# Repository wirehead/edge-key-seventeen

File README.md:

# edge-key-seventeen: A 17 key standard-layout numeric keypad plus encoders

I like numeric keypads.  They come in handy when I am working with CAD packages and stuff.  So you can see this as a piece of quiet rebellion against the world of hipster 40% or 60% fancy keyboards but one that still gives you a durable, fancy, interesting, artisanal, hand-crafted, mechanically-keyed product at the end of it.

## Prior art

This is partially developed using [Ruiqi Mao's Keyboard PCB guide](https://github.com/ruiqimao/keyboard-pcb-guide) as a reference... except that I'd suggest you don't actually use that guide as a reference because it's got some inaccuracies and at this point is old and unmaintained.  It turns out that, because I was designing it around parts that I already was comfortable with using and based it off of prior designs, I'd managed to sidestep all of the problems.  The current hotness is arguably the [ai03 Keyboard PCB](https://wiki.ai03.com/books/pcb-design) guide which seems to be newer and more accurate.

Otherwise, this has design lineage through a few earlier designs I cooked up but won't bother posting because they were mostly design experiments and aren't really useful for anyone.

## The design

### Design goals

* Be mostly standard in being designed for the QMK firmware, use Cherry MX keyswitches and standard-sized keycaps, etc.
* Contain the 17 keys of a numeric keypad, plus maybe some encoders for the funs.
* Look vaguely interesting as just a PCB.
* Use parts I already had in my parts bin for other projects.

### Concrete technical spec

* 17 keys in the standard layout so you can use pretty much any standard-layout numeric keypad caps.
* 2 rotary encoders with push-buttons.
* ATMega32u4 processor
* USB-C port
* Extra ESD protection diodes and a polyfuse for durability
* Programming port that you shouldn't actually need to ever use.
* 9 4-pin SK6812 "NeoPixel" RGB LEDs pointed downward for underglow
* 6 M2.5 mounting holes
* Not quite able to fit in the 10cm x 10cm box because of the size of the keys.
* Puns on the silkscreen

### USB protection

I did a bunch of digging and datasheet reading.

Given that I'm plugging this into the USB port on my computer, I tend to go for safety.  Thus, there's a ESD diode to protect the USB lines from spikes, there's a polyfuse on the power line so it won't use too much power, there's the required capacitors, and there's a decoupling network to keep the EMI from the cable sheath from crossing over to the ground plane.  This is more than most of the development boards.

I also added a polyfuse in case you short power to ground so it will reduce the chances that things go really bad.

### Routing scheme

Col: PF0, PD4, PD5, PD3, PD2
Row: PB6, PC7, PC6. PB5, PB4
Encoders: PF5/PF6, PF1/PF4
Col -> Row

Neopixel: PB7

Numlock LED: PF7

## BOM

|Reference	 |Quantity	 |Value	 |Footprint|
|------------|-----------|-------|---------|
|C10 	| 1	| 4.7 nF	| 0805 |
|C1,C2 	| 2	| 22 pF	| 0805 |
|C3 	| 1	| 10 uF	| 0805 |
|C4 	| 1	| 1 uF	| 0805 |
|C5,C6,C7,C8 	| 4	| 0.1 uF	| 0805 | 
|D1,D2,D3,D4,D5,D6,D7,D9,D10,D11,D12,D13,D14,D15,D16,D17,D18,D27,D28 | 19	1N4148	| SOD123 / Axial |
|D19,D20,D21,D22,D23,D24,D25,D26,D29 	| 9	| SK6812	| 5050 PLCC4 |
|D30    | 1 | 5mm LED | |
|D8 	| 1	| PRTR5V0U2X_215	| TO-253-4 |
|F1 	| 1	| 500 mA Polyfuse	| 1206 |
|H1-H6 	| 6	| Mounting Hole	| M2.5 |
|J1 	| 1	| MicroUSB	| GCT USB4085-GF-A |
|J2 	| 1	| AVR-ISP-6	| 2x03 2.54mm pitch vertical SMD |
|MX1,MX2,MX3,MX4,MX5,MX6,MX7,MX9,MX10,MX11,MX12,MX13,MX14,MX17 | 14	| Cherry MX	|1U |
|MX8 MX15 	| 2	| Cherry MX	| 2U Vertical |
|MX16 	| 1	| Cherry MX	| 2U Horizontal |
|R1 	| 1	| 1M | 0603 |
|R2,R3 	| 2	| 22 | 0603 |
|R4,R5	| 2	| 10k | 0805 |
|R6,R8  | 2 | 5.1k | 0603 | 
|R7 | 1	| 1 M | 0603 |
|R9,R10 | 1	| 330 | 0805 |
|S1 | 1	| Toggle switch	| C&K KSR223GLFG | 
|SW1,SW2 | 2	| Rotary_Encoder_Switch	| PEC11R-4215F-S0024-0-0-0 |
|U1 | 1	| ATMEGA32U4 | TQFP-44 |
|Y1 | 1	| 16 MHz | HC49-U |

## Construction

The gerber files are as I upload to JLCPCB to be fabbed.

If other people start wanting to try and fab this board, I'll write an actual proper assembly guide. :)

Either way, the important points to consider are:

* Everything should be solderable with a regular old temperature-controlled ESD-protected soldering iron.
* You don't need to populate J2 unless you get yourself in deep trouble.
* The keyboard diodes are hybrid footprints that can use either a SOD-123 surface mount diode or an axial one.  I actually find SOD-123's easier to solder all told but I'm probably at least a bit odd.
* You can use either PCB-mount or plate-mount keyswitches and there are holes for PCB-mounted stabilizers.
* You can use a set of Mill-Max 7305-0-15-15-47-27-10-0 maybe the new 3305-1-15-15-47-27-10-0 receptacle connectors so that the keyswitches can be hot-swapped -- The 3305-X series is a new part specifically designed for keyswitches.

### Initial bootstrapping

You should just be able to program a freshly constructed board to the USB port and use the QMK programming tool to put an appropriate firmware on the board with the default bootloader.

I need to actually submit the upstream patches for QMK.

### Mounting holes

There are 6 M2.5 sized mounting holes in semi-convenient locations.

### Chassis design

This will appear later, still working on it!

## Changelog

### v1.0 rev 1

### v1.0 rev 2

* MicroUSB replaced with USB-C
* RS-187R05A2-DS button replaced with KSR223G LFG
* RG-49 Crystal a 3.2x2.5mm SMT 
* KiCAD 6.x instead of KiCAD 5.x

### Things I would change next time

* I might try to trim a few mm off of each of the edges.
* I might remove the hybrid SOD123/Axial feature because I actually solder SOD123's faster than I solder axial parts these days.
* The programming port is kinda annoying in the layout and I guess I need to look at more alternatives in the rare case you need to bootloader it.

## License

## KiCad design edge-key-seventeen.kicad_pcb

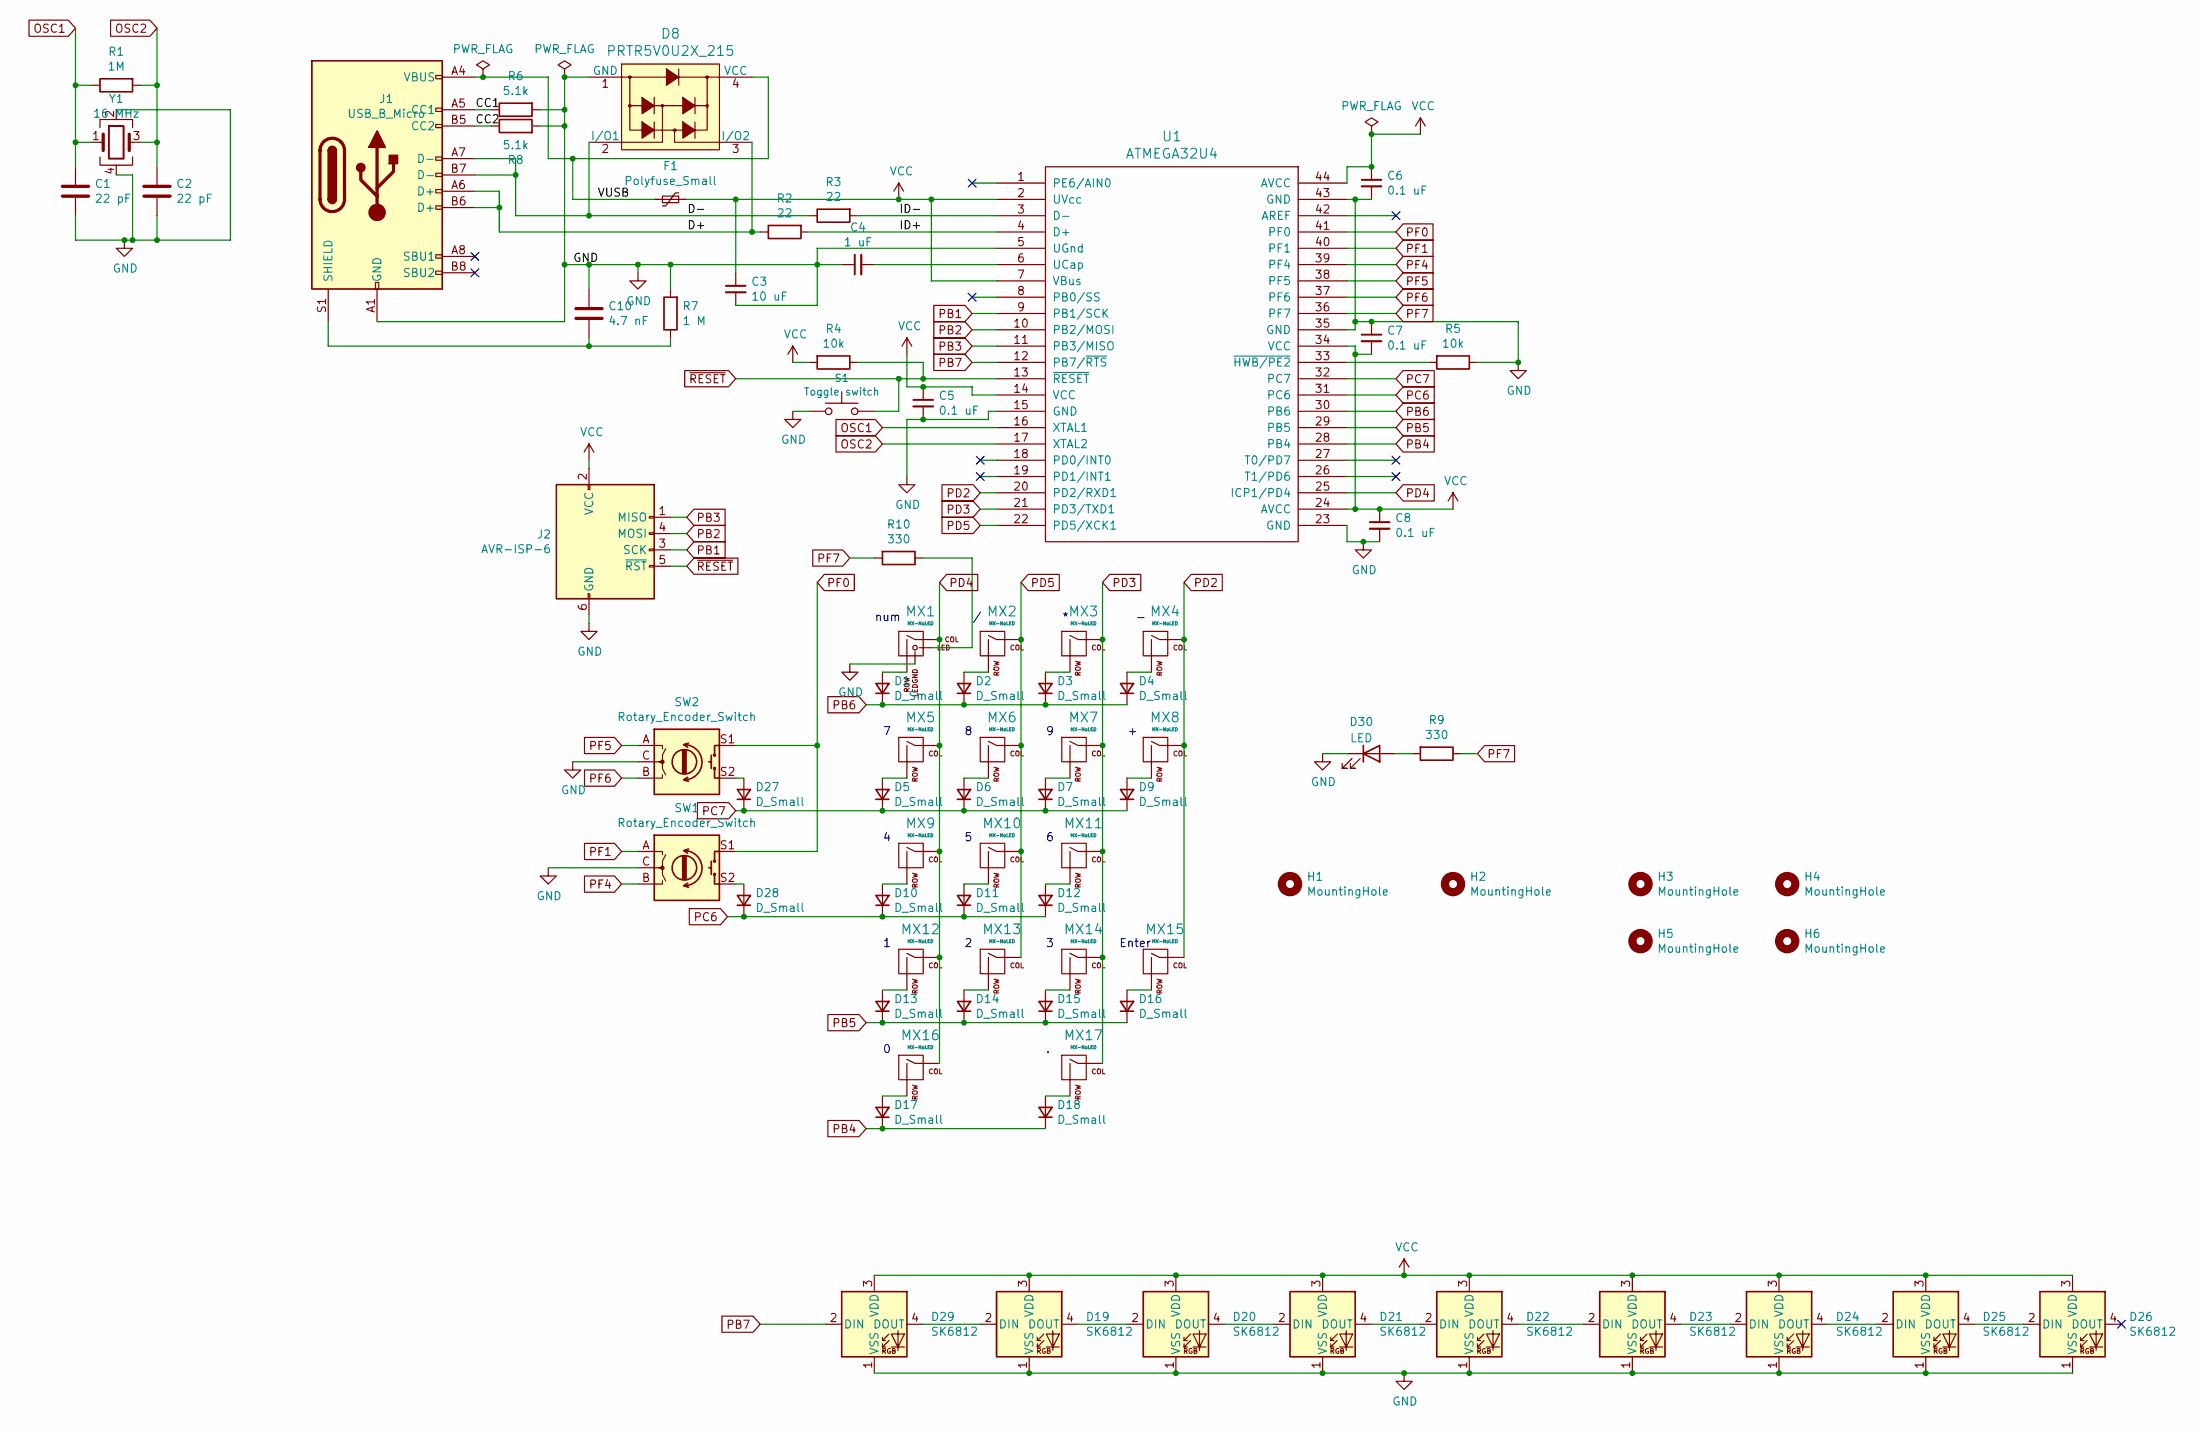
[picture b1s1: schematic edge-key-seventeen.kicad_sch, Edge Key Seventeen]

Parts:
C1, C2: 22 pF; C_0805_2012Metric_Pad1.15x1.40mm_HandSolder
C3: 10 uF; C_0805_2012Metric_Pad1.15x1.40mm_HandSolder
C4: 1 uF; C_0805_2012Metric_Pad1.15x1.40mm_HandSolder
C5, C6, C7, C8: 0.1 uF; C_0603_1608Metric_Pad1.08x0.95mm_HandSolder
C10: 4.7 nF; C_0603_1608Metric_Pad1.08x0.95mm_HandSolder
D1, D2, D3, D4, D5, D6, D7, D9, D10, D11, D12, D13, D14, D15, D16, D17, D18, D27, D28: D_Small; D_SOD123_axial
D8: PRTR5V0U2X_215; SOT-143_Handsoldering; MPN PRTR5V0U2X,215; Digi-Key_PN 1727-3884-1-ND
D19, D20, D21, D22, D23, D24, D25, D26, D29: SK6812; LED_SK6812_PLCC4_5.0x5.0mm_P3.2mm
D30: LED; LED_D5.0mm
F1: Polyfuse_Small; Fuse_1206_3216Metric_Pad1.42x1.75mm_HandSolder
H1, H2, H3, H4, H5, H6: MountingHole; MountingHole_2.7mm_M2.5
J1: USB_B_Micro; USB_C_Receptacle_GCT_USB4085
J2: AVR-ISP-6; PinHeader_2x03_P2.54mm_Vertical_SMD
MX1: MX-NoLED; MXOnly-1U
MX2, MX3, MX4, MX5, MX6, MX7, MX9, MX10, MX11, MX12, MX13, MX14, MX17: MX-NoLED; MXOnly-1U-NoLED
MX8, MX15: MX-NoLED; SW_Cherry_MX_2.00u_Vertical_PCB_nosilk
MX16: MX-NoLED; MXOnly-2U-NoLED
R1: 1M; R_0603_1608Metric_Pad0.98x0.95mm_HandSolder
R2, R3: 22; R_0603_1608Metric_Pad0.98x0.95mm_HandSolder
R4: 10k; R_0805_2012Metric_Pad1.15x1.40mm_HandSolder
R5: 10k; R_0805_2012Metric_Pad1.20x1.40mm_HandSolder
R6, R8: 5.1k; R_0603_1608Metric_Pad0.98x0.95mm_HandSolder
R7: 1 M; R_0603_1608Metric_Pad0.98x0.95mm_HandSolder
R9, R10: 330; R_0805_2012Metric_Pad1.20x1.40mm_HandSolder
S1: Toggle switch; SW_KSR223GLFG
SW1, SW2: Rotary_Encoder_Switch; Bourns-PEC11R-4215F-S0024-0-0-0
U1: ATMEGA32U4; TQFP-44_10x10mm_P0.8mm
Y1: 16 MHz; Crystal_SMD_3225-4Pin_3.2x2.5mm_HandSoldering

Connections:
/CC1: J1.A5 (CC1), R6.1
/CC2: J1.B5 (CC2), R8.1
/D+: D8.3 (I/O2), J1.A6 (D+), J1.B6 (D+), R2.1
/D-: D8.2 (I/O1), J1.A7 (D-), J1.B7 (D-), R3.1
/ID+: R2.2, U1.4 (D+)
/ID-: R3.2, U1.3 (D-)
/VUSB: D8.4 (VCC), F1.2, J1.A4 (VBUS), J1.A9 (VBUS), J1.B4 (VBUS), J1.B9 (VBUS)
GND: C1.2, C2.2, C3.2, C4.1, C5.2, C6.2, C7.1, C8.2, C10.2, D8.1 (GND), D19.1 (VSS), D20.1 (VSS), D21.1 (VSS), D22.1 (VSS), D23.1 (VSS), D24.1 (VSS), D25.1 (VSS), D26.1 (VSS), D29.1 (VSS), D30.1 (K), J1.A1 (GND), J1.A12 (GND), J1.B1 (GND), J1.B12 (GND), J2.6 (GND), MX1.4 (LEDGND), R5.1, R6.2, R7.2, R8.2, S1.2, SW1.C, SW2.C, U1.5 (UGnd), U1.15 (GND), U1.23 (GND), U1.35 (GND), U1.43 (GND), Y1.2, Y1.4
unnamed: C4.2, U1.6 (UCap)
unnamed: C10.1, J1.S1 (SHIELD), R7.1
unnamed: D1.2 (A), MX1.2 (ROW)
unnamed: D2.2 (A), MX2.2 (ROW)
unnamed: D3.2 (A), MX3.2 (ROW)
unnamed: D4.2 (A), MX4.2 (ROW)
unnamed: D5.2 (A), MX5.2 (ROW)
unnamed: D6.2 (A), MX6.2 (ROW)
unnamed: D7.2 (A), MX7.2 (ROW)
unnamed: D9.2 (A), MX8.2 (ROW)
unnamed: D10.2 (A), MX9.2 (ROW)
unnamed: D11.2 (A), MX10.2 (ROW)
unnamed: D12.2 (A), MX11.2 (ROW)
unnamed: D13.2 (A), MX12.2 (ROW)
unnamed: D14.2 (A), MX13.2 (ROW)
unnamed: D15.2 (A), MX14.2 (ROW)
unnamed: D16.2 (A), MX15.2 (ROW)
unnamed: D17.2 (A), MX16.2 (ROW)
unnamed: D18.2 (A), MX17.2 (ROW)
unnamed: D19.2 (DIN), D29.4 (DOUT)
unnamed: D19.4 (DOUT), D20.2 (DIN)
unnamed: D20.4 (DOUT), D21.2 (DIN)
unnamed: D21.4 (DOUT), D22.2 (DIN)
unnamed: D22.4 (DOUT), D23.2 (DIN)
unnamed: D23.4 (DOUT), D24.2 (DIN)
unnamed: D24.4 (DOUT), D25.2 (DIN)
unnamed: D25.4 (DOUT), D26.2 (DIN)
unnamed: D27.2 (A), SW2.S2
unnamed: D28.2 (A), SW1.S2
unnamed: D30.2 (A), R9.2
unnamed: MX1.3 (LED), R10.1
unnamed: R5.2, U1.33 (~HWB/PE2)
OSC1: C1.1, R1.1, U1.16 (XTAL1), Y1.1
OSC2: C2.1, R1.2, U1.17 (XTAL2), Y1.3
PB1: J2.3 (SCK), U1.9 (PB1/SCK)
PB2: J2.4 (MOSI), U1.10 (PB2/MOSI)
PB3: J2.1 (MISO), U1.11 (PB3/MISO)
PB4: D17.1 (K), D18.1 (K), U1.28 (PB4)
PB5: D13.1 (K), D14.1 (K), D15.1 (K), D16.1 (K), U1.29 (PB5)
PB6: D1.1 (K), D2.1 (K), D3.1 (K), D4.1 (K), U1.30 (PB6)
PB7: D29.2 (DIN), U1.12 (PB7/~RTS)
PC6: D10.1 (K), D11.1 (K), D12.1 (K), D28.1 (K), U1.31 (PC6)
PC7: D5.1 (K), D6.1 (K), D7.1 (K), D9.1 (K), D27.1 (K), U1.32 (PC7)
PD2: MX4.1 (COL), MX8.1 (COL), MX15.1 (COL), U1.20 (PD2/RXD1)
PD3: MX3.1 (COL), MX7.1 (COL), MX11.1 (COL), MX14.1 (COL), MX17.1 (COL), U1.21 (PD3/TXD1)
PD4: MX1.1 (COL), MX5.1 (COL), MX9.1 (COL), MX12.1 (COL), MX16.1 (COL), U1.25 (ICP1/PD4)
PD5: MX2.1 (COL), MX6.1 (COL), MX10.1 (COL), MX13.1 (COL), U1.22 (PD5/XCK1)
PF0: SW1.S1, SW2.S1, U1.41 (PF0)
PF1: SW1.A, U1.40 (PF1)
PF4: SW1.B, U1.39 (PF4)
PF5: SW2.A, U1.38 (PF5)
PF6: SW2.B, U1.37 (PF6)
PF7: R9.1, R10.2, U1.36 (PF7)
VCC: C3.1, C5.1, C6.1, C7.2, C8.1, D19.3 (VDD), D20.3 (VDD), D21.3 (VDD), D22.3 (VDD), D23.3 (VDD), D24.3 (VDD), D25.3 (VDD), D26.3 (VDD), D29.3 (VDD), F1.1, J2.2 (VCC), R4.2, U1.2 (UVcc), U1.7 (VBus), U1.14 (VCC), U1.24 (AVCC), U1.34 (VCC), U1.44 (AVCC)
~RESET: J2.5 (~RST), R4.1, S1.1, U1.13 (~RESET)

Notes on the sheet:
Enter
num

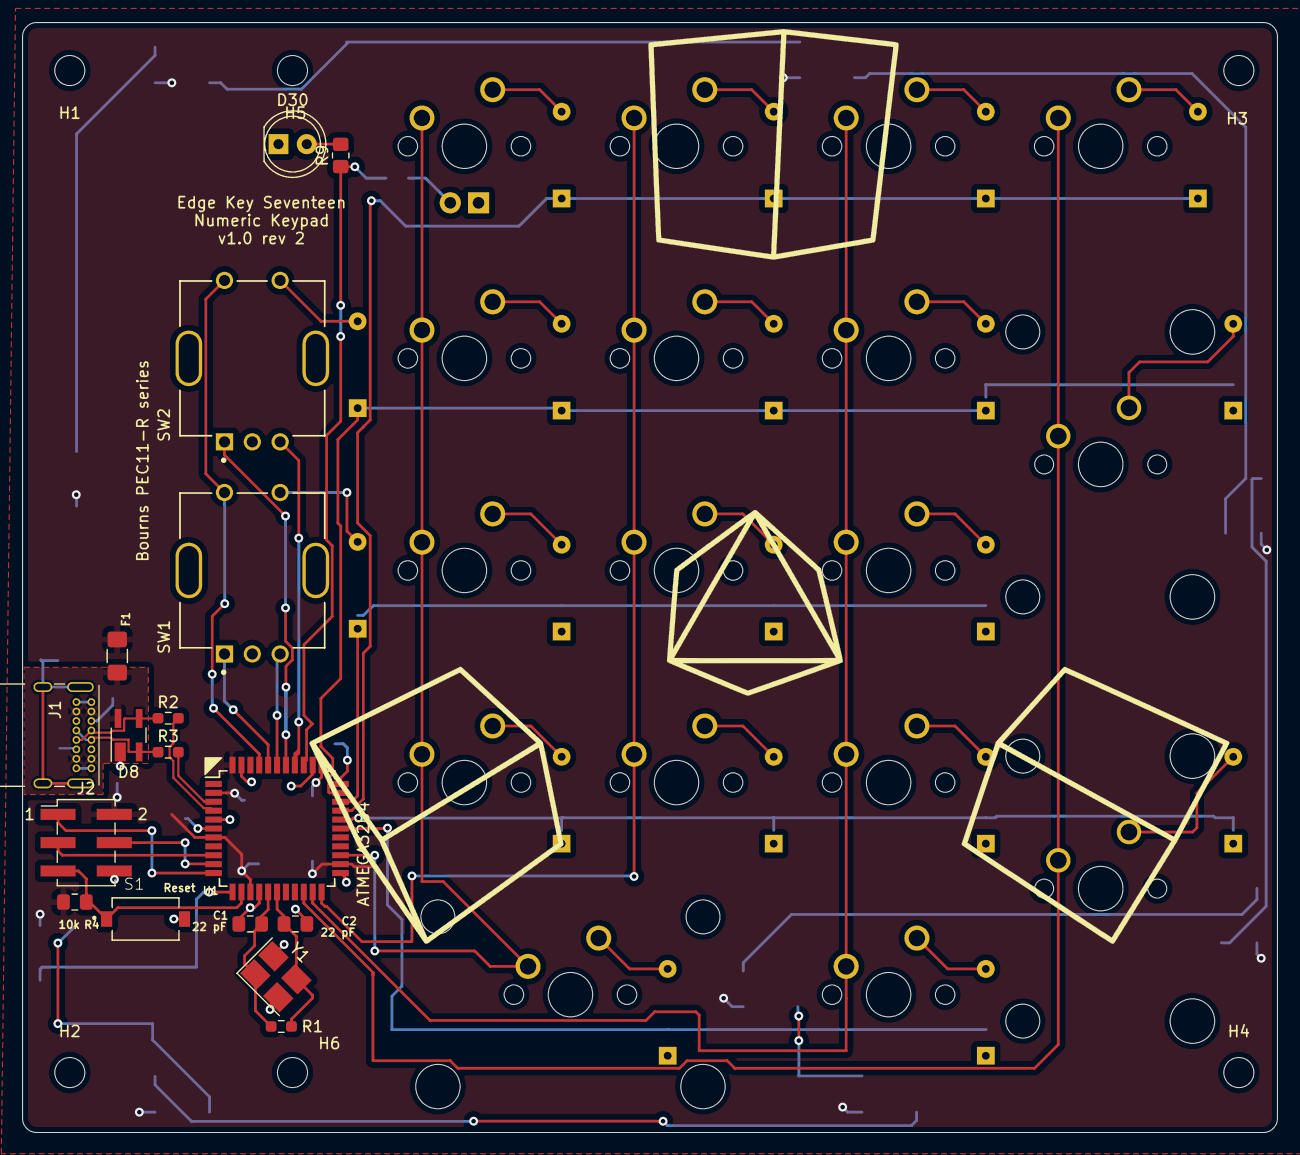
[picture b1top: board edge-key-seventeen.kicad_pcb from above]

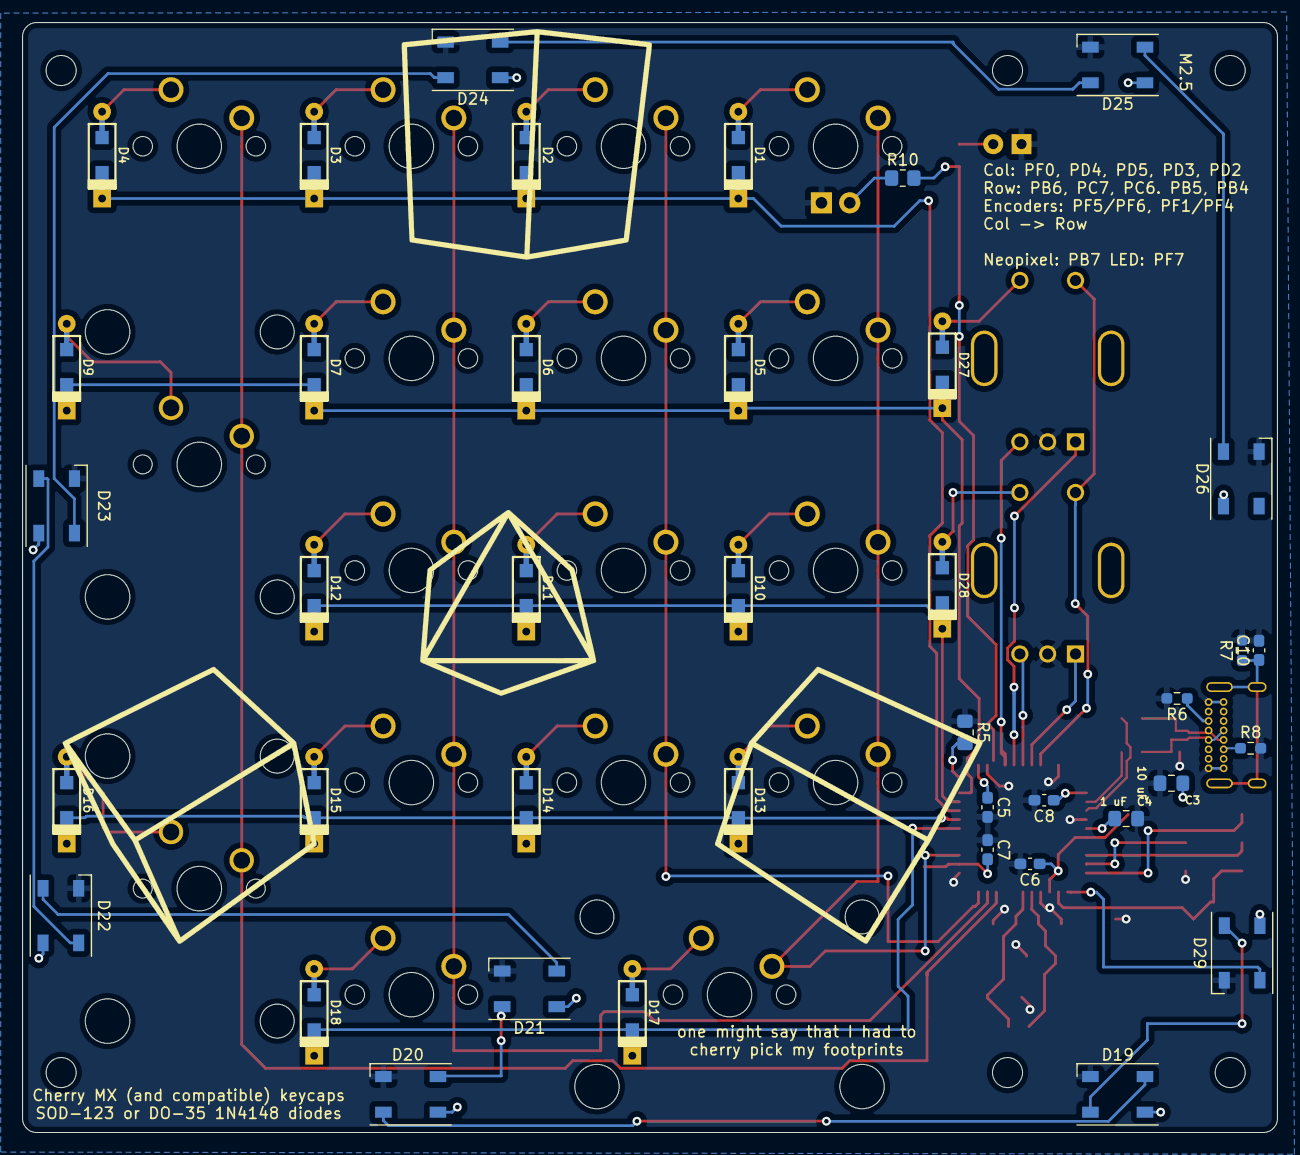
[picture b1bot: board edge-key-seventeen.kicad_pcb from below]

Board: 2 copper layers, 112.7 x 99.7 mm, 82 parts (41 on the bottom side), 63 nets.

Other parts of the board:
Ref**: Val**; keyboard-bit
Ref**#2: Val**; keyboard-bit

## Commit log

2025-05-03 update.

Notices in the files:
README.md:
License:
[License: CC BY-SA 4.0](https://creativecommons.org/licenses/by-sa/4.0/)
